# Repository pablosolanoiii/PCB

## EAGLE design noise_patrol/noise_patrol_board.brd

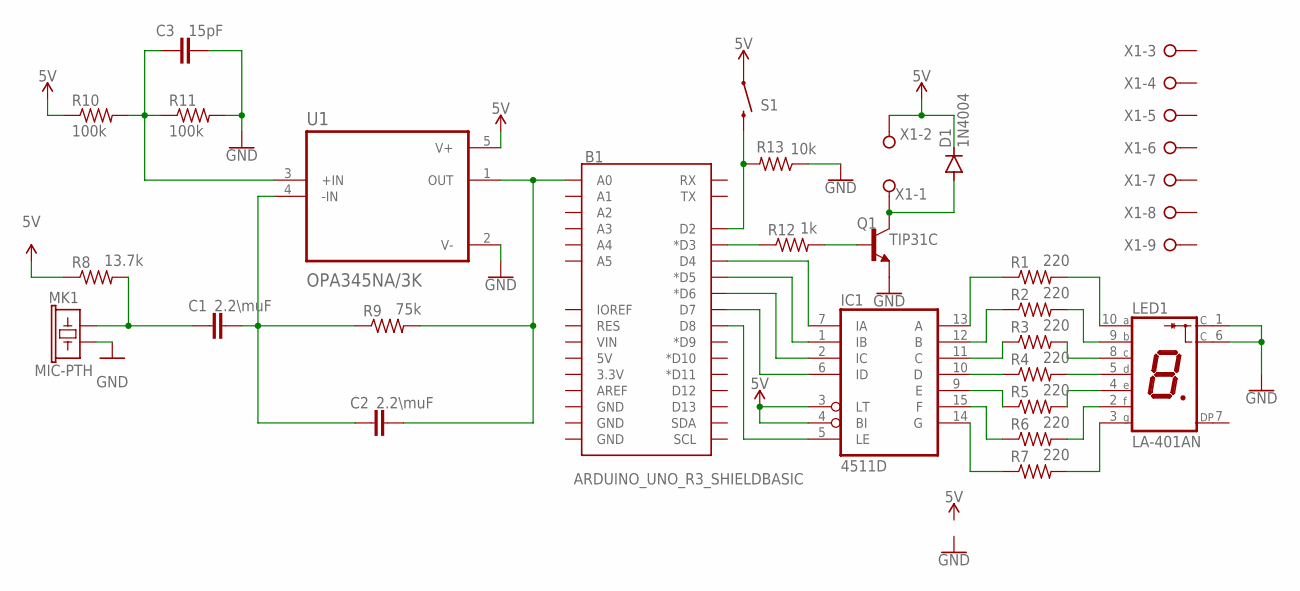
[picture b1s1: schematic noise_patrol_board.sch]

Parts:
B1: ARDUINO_UNO_R3_SHIELDBASIC; UNO_R3_SHIELD
C1, C2: 2.2\muF; 0603
C3: 15pF; 0603
D1: 1N4004; DO41-10
IC1: 4511D; SO16
LED1: LA-401AN; LA-401
MK1: MIC-PTH; MICROPHONE-PTH-9.7MM
Q1: TIP31C; TO220
R1, R2, R3, R4, R5, R6, R7: 220; 0204/7
R8: 13.7k; M1206
R9: 75k; M1206
R10, R11: 100k; M1206
R12: 1k; M1206
R13: 10k; M1206
S1: Reset button; TACTILE_SWITCH_PTH_6.0MM
U1: OPA345NA/3K; SOT95P280X145-5N
X1: W237-09P; W237-9P

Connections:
5V: D1.C, IC1.3 (LT), IC1.4 (BI), R8.1, R10.1, S1.1, U1.5 (V+), X1.2
GND: C3.2, LED1.1 (C), LED1.6 (C), MK1.GND (2), Q1.3 (E), R11.2, R13.1, U1.2 (V-)
unnamed: IC1.12 (B), R2.1
unnamed: IC1.11 (C), R3.1
unnamed: IC1.10 (D), R4.1
unnamed: IC1.9 (E), R5.1
unnamed: IC1.15 (F), R6.1
unnamed: IC1.14 (G), R7.1
unnamed: LED1.3 (G), R7.2
unnamed: LED1.2 (F), R6.2
unnamed: LED1.4 (E), R5.2
unnamed: LED1.5 (D), R4.2
unnamed: LED1.8 (C), R3.2
unnamed: LED1.9 (B), R2.2
unnamed: LED1.10 (A), R1.2
unnamed: B1.D4, IC1.7 (IA)
unnamed: B1.D5 (*D5), IC1.1 (IB)
unnamed: B1.D6 (*D6), IC1.2 (IC)
unnamed: B1.D7, IC1.6 (ID)
unnamed: B1.A0, C2.2, R9.2, U1.1 (OUT)
unnamed: B1.D8, IC1.5 (LE)
unnamed: C1.1, MK1.OUT (1), R8.2
unnamed: C1.2, C2.1, R9.1, U1.4 (-IN)
unnamed: B1.D3 (*D3), R12.1
unnamed: Q1.1 (B), R12.2
unnamed: C3.1, R10.2, R11.1, U1.3 (+IN)
unnamed: D1.A, Q1.2 (C), X1.1
unnamed: B1.D2, R13.2, S1.3 (2)
TOOL: IC1.13 (A), R1.1
VDD: IC1.16 (VDD)
VSS: IC1.8 (VSS)

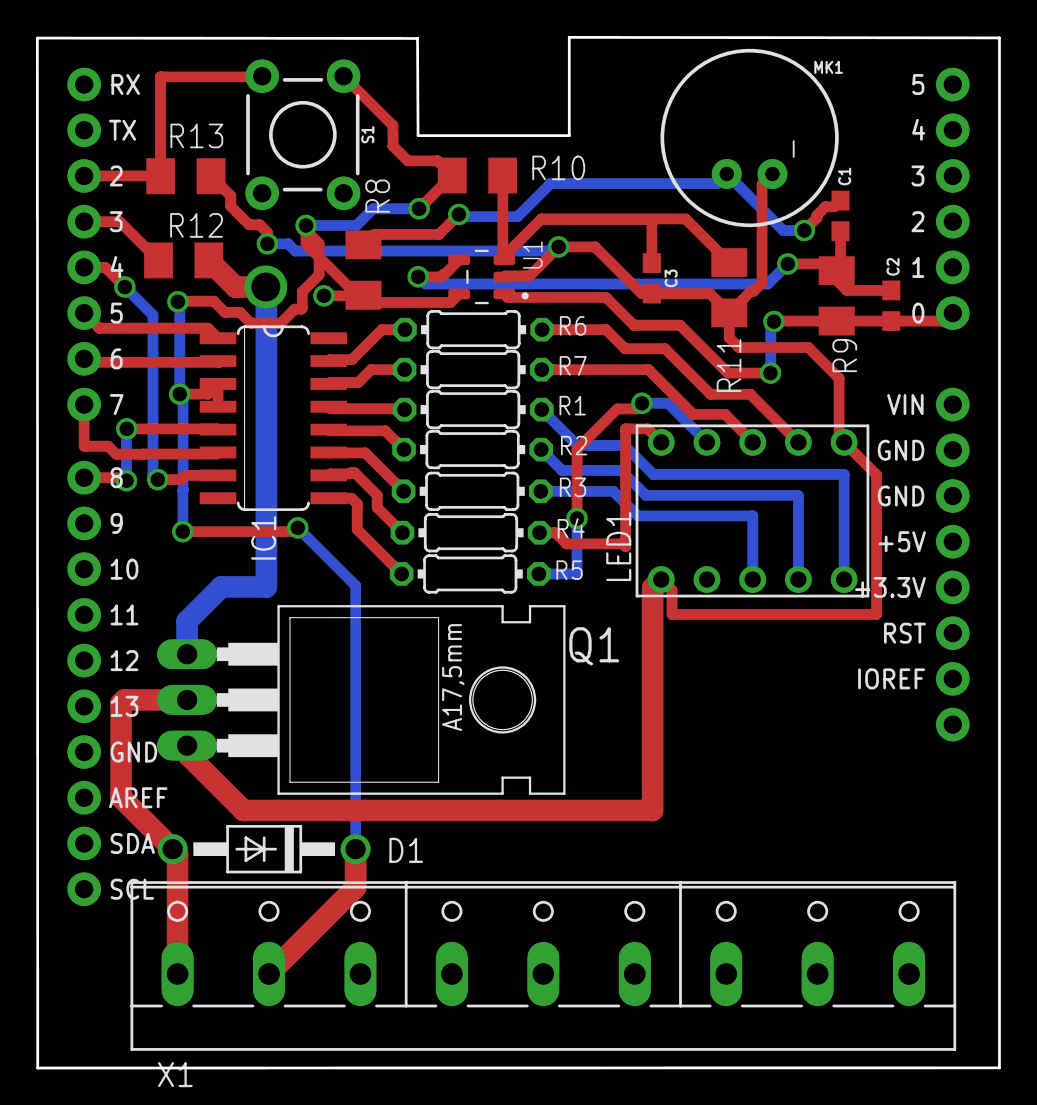
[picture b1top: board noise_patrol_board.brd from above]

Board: 2 copper layers, 53.5 x 57.3 mm, 25 parts (0 on the bottom side), 29 nets.

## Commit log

2026-05-04 initial setup
2026-05-04 Added Some Parts
2026-05-05 Saving Progress: Added More parts and starting to understand the software
2026-05-06 Starting to Rearrange the board
2026-05-07 Finished getting everything on to the board
2026-05-07 Schematic PDF
2026-05-08 Finished
2026-05-08 Final Product
2026-05-08 DRC File
2026-05-16 Final

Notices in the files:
parts and their libraries:
SparkFun-Boards: Licensing: Creative Commons ShareAlike 4.0 International - https://creativecommons.org/licenses/by-sa/4.0
